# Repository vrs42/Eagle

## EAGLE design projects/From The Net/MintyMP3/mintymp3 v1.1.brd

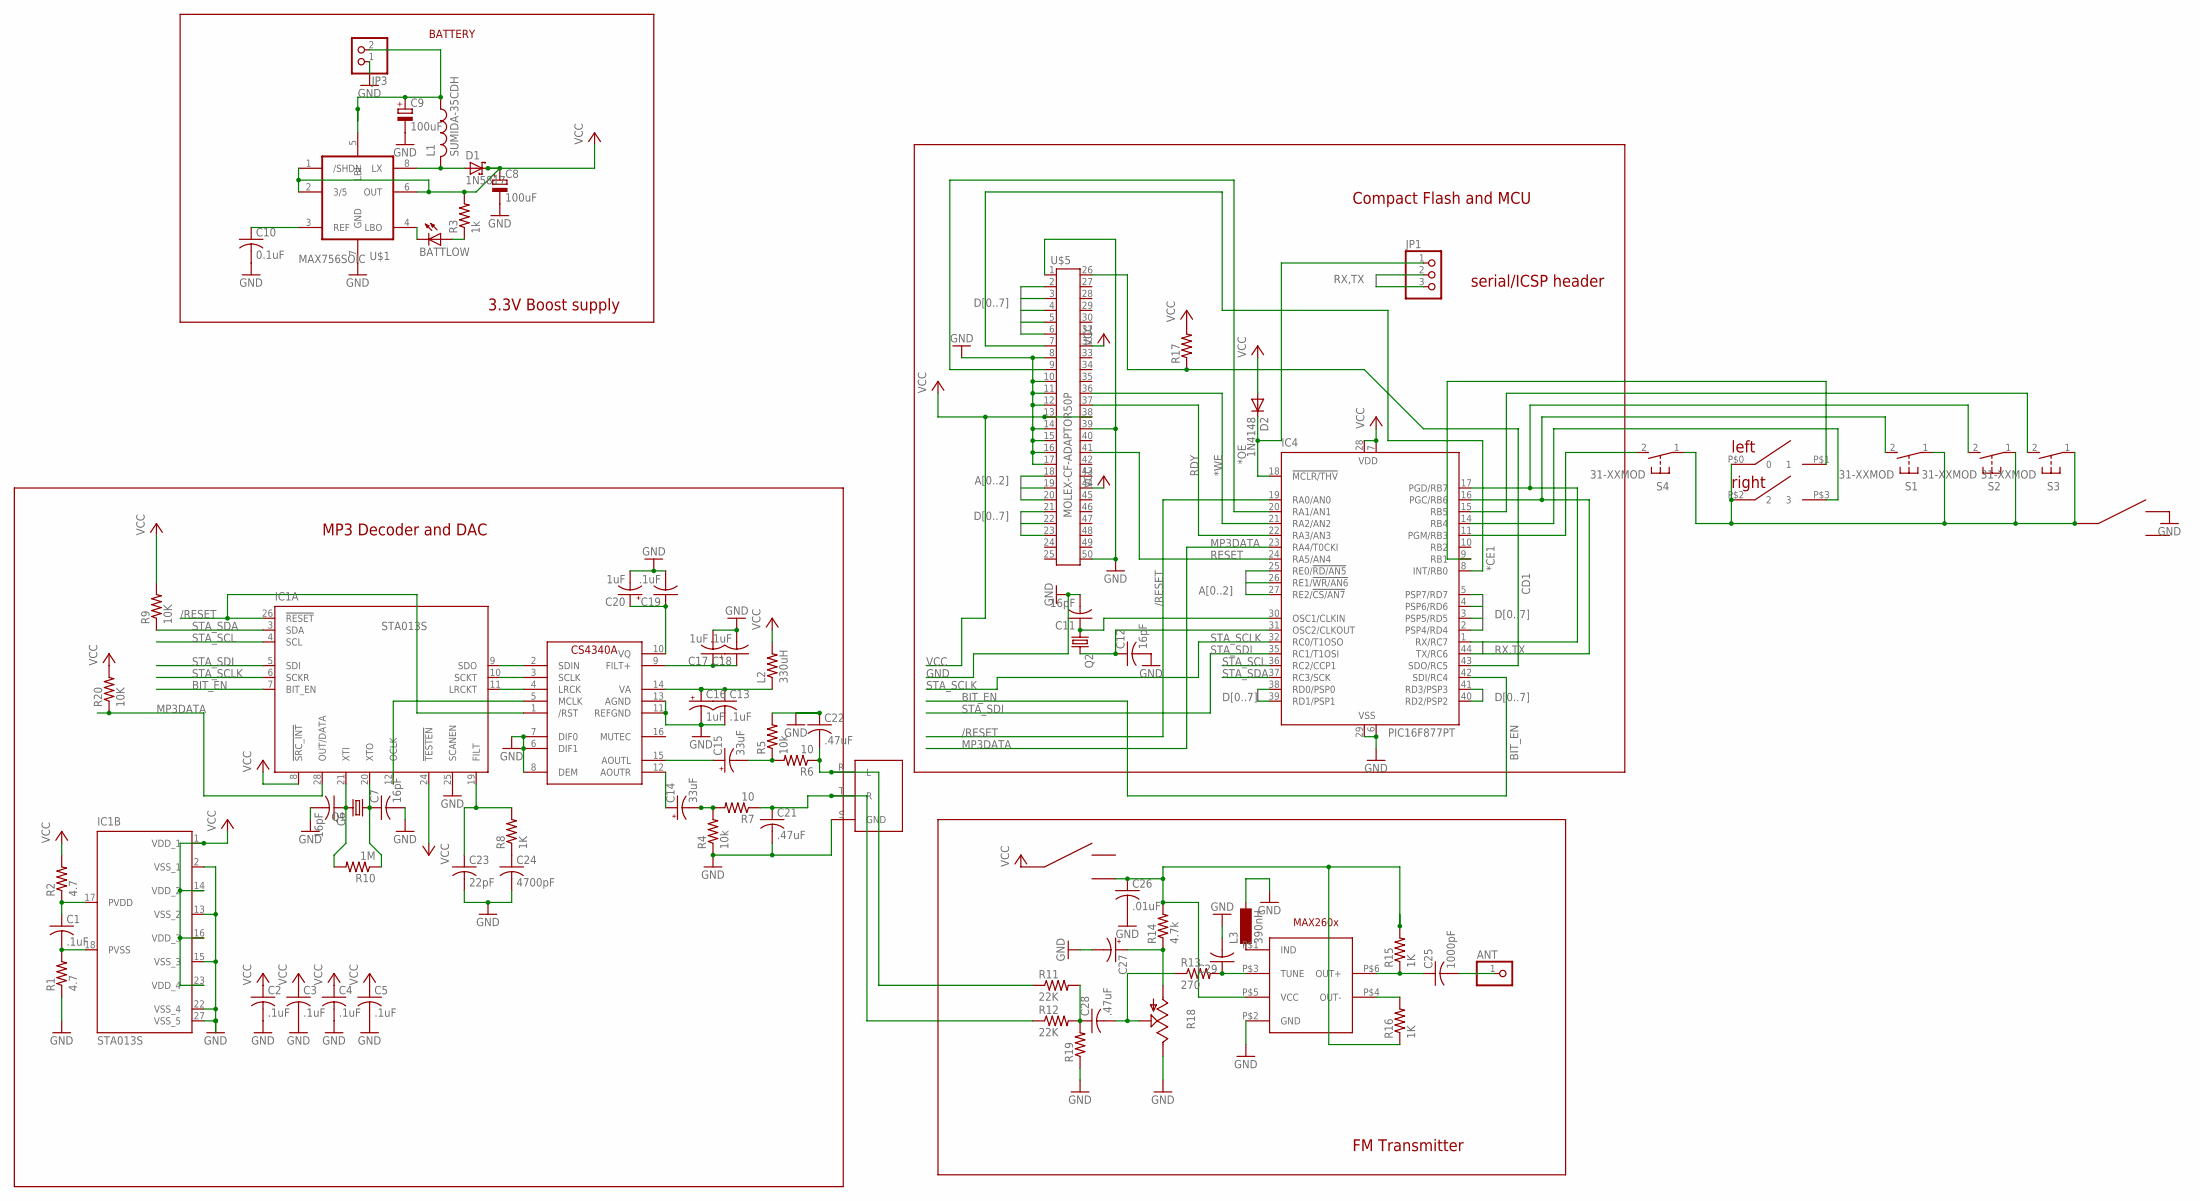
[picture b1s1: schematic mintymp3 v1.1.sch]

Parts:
ANT: PINHD-1X1; 1X01
BATTLOW: LED3MM
C1, C2, C3, C4, C5, C13, C18, C19: .1uF; C1206
C6, C7, C11, C12: 16pF; C1206
C8, C9: 100uF; PANASONIC_D
C10: 0.1uF; C1206
C14, C15: 33uF; PANASONIC_B
C16, C17, C20: 1uF; PANASONIC_A
C21, C22, C28: .47uF; C1206
C23: 22pF; C1206
C24: 4700pF; C1206
C25: 1000pF; C1206
C26: .01uF; C1206
C27: CPOL-USB; PANASONIC_B
C29: C-USC1206; C1206
D1: 1N5817; DO35-7
D2: 1N4148; DO35-10
FM_SWITCH: SLIDE_SW; SLIDESWITCH
HEADPHONE: STEREOJACKSMDMOD; SJ-3523-MODIFIED
IC1: STA013S; SO28W
IC4: PIC16F877PT; TQFP44
JP1: PINHD-1X3; 1X03
JP3: PINHD-1X2; 1X02
L1: SUMIDA-35CDH; CDH53
L2: 330uH; R1210
L3: 390nH; SM-1206
Q1, Q2: CRYSTALHC49UP; HC49UP
R1, R2: 4.7; R1206
R3: 1k; R1206
R4, R5: 10k; R1206
R6, R7: 10; R1206
R8, R15, R16: 1K; R1206
R9, R20: 10K; R1206
R10: 1M; R1206
R11, R12: 22K; R1206
R13: 270; R1206
R14: 4.7k; R1206
R17, R19: R-US_R1206; R1206
R18: TRIM_US-ECP10P; ECP10P
S1, S2, S3, S4: 31-XXMOD; B3F-31XX-MODIFIED
U$1: MAX756SOIC; SO08
U$2: SLIDE_SW; SLIDESWITCH
U$3: TPC_SWITCH; TPC_SCAN
U$4: CS4340A; SO16
U$5: MOLEX-CF-ADAPTOR50P; COMPACTFLASH
U$9: MAX260X; SOT23-6

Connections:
*CE1: IC4.8 (INT/RB0), U$5.7
*OE: IC4.20 (RA1/AN1), U$5.9
*WE: IC4.21 (RA2/AN2), U$5.36
/RESET: IC1.26 (!RESET), IC4.19 (RA0/AN0), U$4.1 (/RST)
A0: IC4.25 (RE0/!RD/AN5), U$5.20
A1: IC4.26 (RE1/!WR/AN6), U$5.19
A2: IC4.27 (RE2/!CS/AN7), U$5.18
ANTENNA: ANT.1, C25.2
BIT_EN: IC1.7 (BIT_EN), IC4.42 (SDI/RC4)
BUTTON1: IC4.11 (PGM/RB3), S4.2 (S)
CD1: IC4.43 (SDO/RC5), R17.1, U$5.26
D0: IC4.38 (RD0/PSP0), U$5.21
D1: IC4.39 (RD1/PSP1), U$5.22
D2: IC4.40 (RD2/PSP2), U$5.23
D3: IC4.41 (RD3/PSP3), U$5.2
D4: IC4.2 (PSP4/RD4), U$5.3
D5: IC4.3 (PSP5/RD5), U$5.4
D6: IC4.4 (PSP6/RD6), U$5.5
D7: IC4.5 (PSP7/RD7), U$5.6
GND: C2.2, C3.2, C4.2, C5.2, C6.2, C7.2, C8.-, C9.-, C10.2, C11.2, C12.2, C13.2, C16.-, C17.-, C18.2, C19.2, C20.-, C21.2, C22.1, C23.2, C24.2, C26.2, C27.-, C29.2, HEADPHONE.S (GND), IC1.2 (VSS_1), IC1.13 (VSS_2), IC1.15 (VSS_3), IC1.22 (VSS_4), IC1.25 (SCANEN), IC1.27 (VSS_5), IC4.6 (VSS), IC4.29 (VSS), JP3.1, L3.2, R1.1, R4.1, R5.2, R18.E, R19.1, U$1.7 (GND), U$2.P$1, U$4.6 (DIF1), U$4.7 (DIF0), U$4.8 (DEM), U$4.11 (REFGND), U$4.13 (AGND), U$5.1, U$5.8, U$5.10, U$5.11, U$5.12, U$5.14, U$5.15, U$5.16, U$5.17, U$5.39, U$5.50, U$9.P$2 (GND)
MCLR: D2.C, IC4.18 (!MCLR/THV), JP1.1
MP3DATA: IC1.28 (OUT/DATA), IC4.23 (RA4/T0CKI), R20.1
unnamed: C26.1, FM_SWITCH.P$3, R14.2, R15.2, R16.1, U$9.P$5 (VCC)
unnamed: C6.1, IC1.21 (XTI), Q1.2, R10.2
unnamed: C7.1, IC1.20 (XTO), Q1.1, R10.1
unnamed: IC4.14 (RB4), U$3.P$3 (3)
unnamed: C1.1, IC1.17 (PVDD), R2.1
unnamed: C1.2, IC1.18 (PVSS), R1.2
unnamed: C9.+, JP3.2, L1.P$1 (1), U$1.5 (LBI)
unnamed: D1.A, L1.P$2 (2), U$1.8 (LX)
unnamed: IC1.9 (SDO), U$4.2 (SDIN)
unnamed: IC1.10 (SCKT), U$4.3 (SCLK)
unnamed: IC1.11 (LRCKT), U$4.4 (LRCK)
unnamed: IC1.12 (OCLK), U$4.5 (MCLK)
unnamed: IC4.9 (RB1), U$3.P$1 (1)
unnamed: IC4.15 (RB5), S3.2 (S)
unnamed: C15.+, U$4.15 (AOUTL)
unnamed: C10.1, U$1.3 (REF)
unnamed: BATTLOW.A, R3.1
unnamed: BATTLOW.K (C), U$1.4 (LBO)
unnamed: C13.1, C16.+, L2.1, U$4.14 (VA)
unnamed: C11.1, IC4.30 (OSC1/CLKIN), Q2.1
unnamed: C12.1, IC4.31 (OSC2/CLKOUT), Q2.2
unnamed: C14.+, U$4.12 (AOUTR)
unnamed: C14.-, R4.2, R7.2
unnamed: C15.-, R5.1, R6.2
unnamed: C22.2, HEADPHONE.R (L), R6.1, R11.1
unnamed: C17.+, C18.1, U$4.9 (FILT+)
unnamed: C19.1, C20.+, U$4.10 (VQ)
unnamed: C29.1, R13.2, U$9.P$3 (TUNE)
unnamed: C24.1, R8.1
unnamed: C23.1, IC1.19 (FILT), R8.2
unnamed: C25.1, R15.1, U$9.P$6 (OUT+)
unnamed: R16.2, U$9.P$4 (OUT-)
unnamed: C21.1, HEADPHONE.T (R), R7.1, R12.1
unnamed: C28.1, R11.2, R12.2, R19.2
unnamed: C27.+, R14.1, R18.A
unnamed: C28.2, R13.1, R18.S
unnamed: L3.1, U$9.P$1 (IND)
unnamed: S1.1, S2.1, S3.1, S4.1, U$2.P$2, U$3.P$0 (0), U$3.P$2 (2)
RDY: IC4.22 (RA3/AN3), U$5.37
RESET: IC4.24 (RA5/AN4), U$5.41
RX: IC4.1 (RX/RC7), IC4.17 (PGD/RB7), JP1.2, S2.2 (S)
STA_SCL: IC1.4 (SCL), IC4.36 (RC2/CCP1)
STA_SCLK: IC1.6 (SCKR), IC4.32 (RC0/T1OSO)
STA_SDA: IC1.3 (SDA), IC4.37 (RC3/SCK), R9.1
STA_SDI: IC1.5 (SDI), IC4.35 (RC1/T1OSI)
TX: IC4.16 (PGC/RB6), IC4.44 (TX/RC6), JP1.3, S1.2 (S)
VCC: C2.1, C3.1, C4.1, C5.1, C8.+, D1.C, D2.A, FM_SWITCH.P$2, IC1.1 (VDD_1), IC1.8 (!SRC_INT), IC1.14 (VDD_2), IC1.16 (VDD_3), IC1.23 (VDD_4), IC1.24 (!TESTEN), IC4.7 (VDD), IC4.28 (VDD), L2.2, R2.2, R3.2, R9.2, R17.2, R20.2, U$1.1 (/SHDN), U$1.2 (3/5), U$1.6 (OUT), U$5.13, U$5.32, U$5.38, U$5.44

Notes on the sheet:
3.3V Boost supply
BATTERY
Compact Flash and MCU
MP3 Decoder and DAC
FM Transmitter
serial/ICSP header

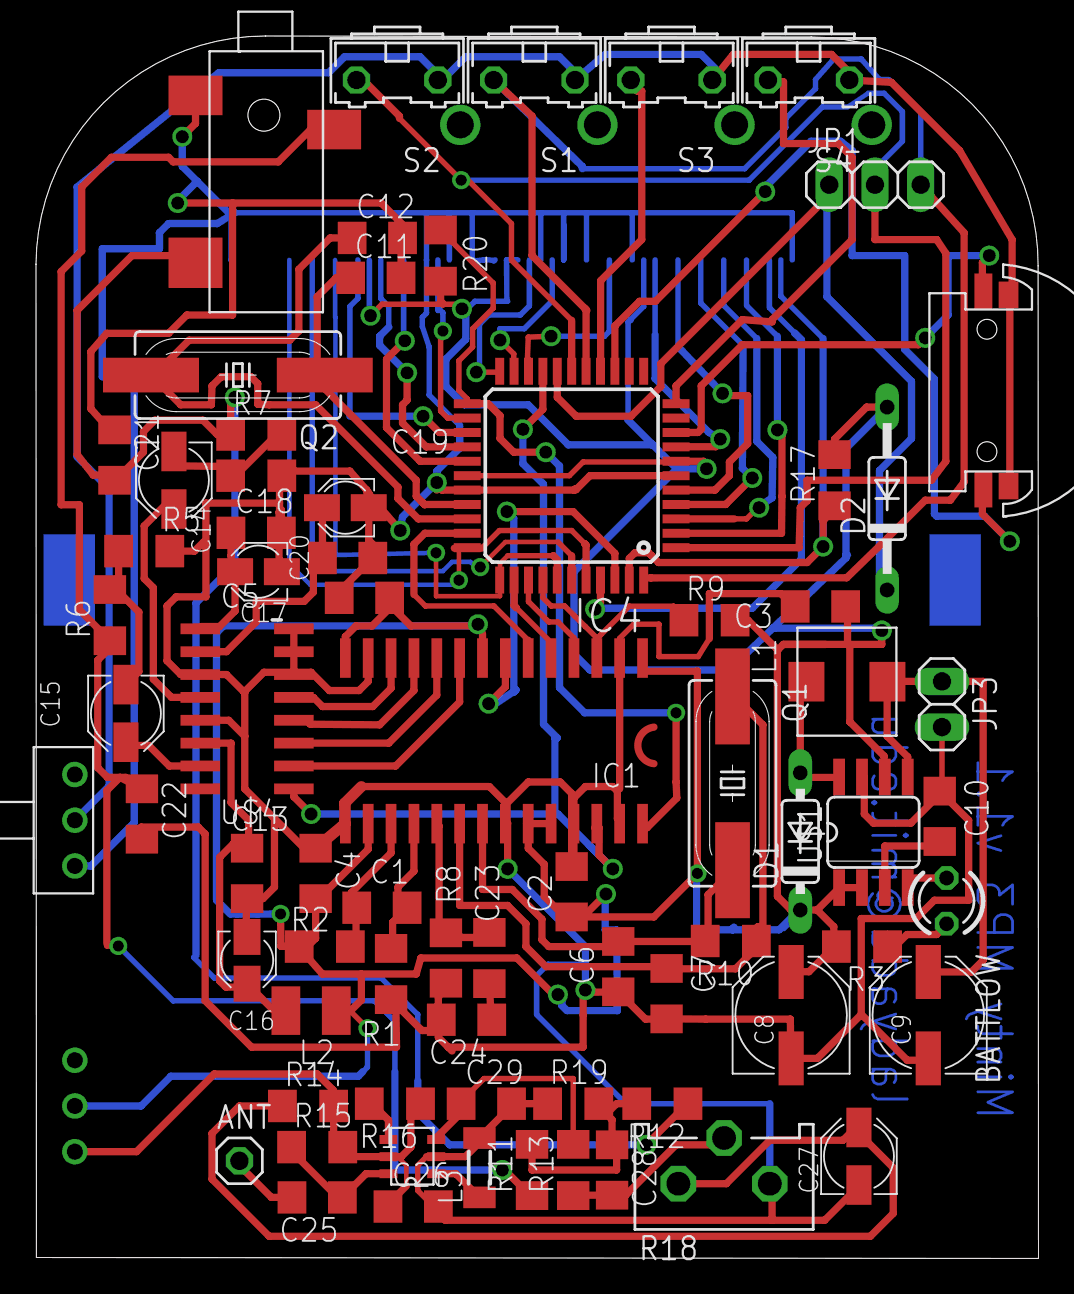
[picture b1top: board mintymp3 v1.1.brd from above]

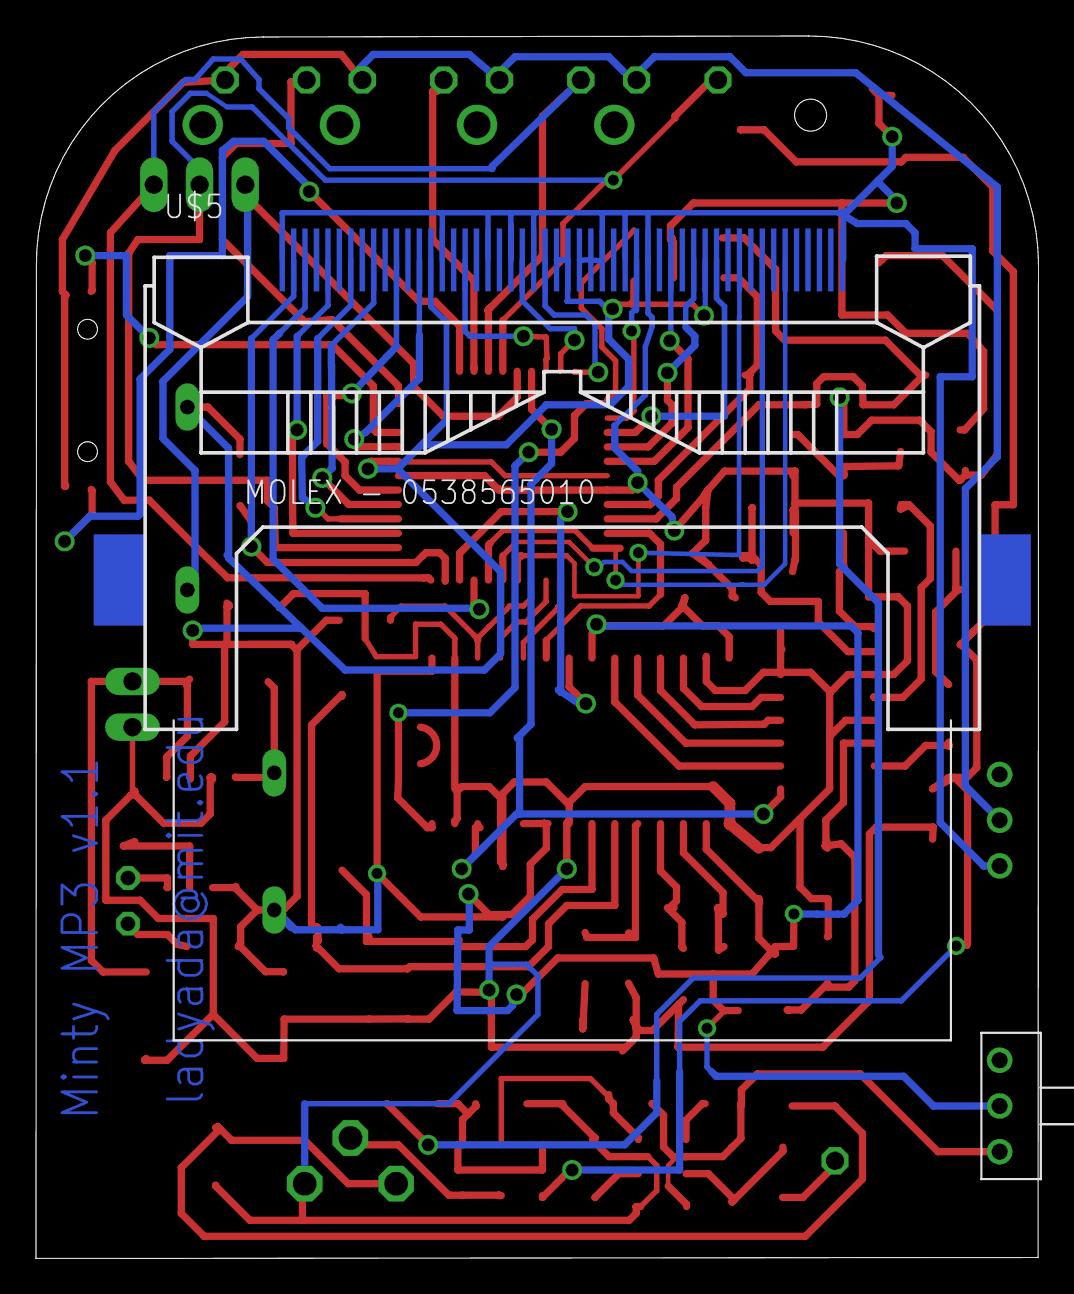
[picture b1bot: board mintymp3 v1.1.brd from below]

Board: 2 copper layers, 55.7 x 67.9 mm, 74 parts (2 on the bottom side), 69 nets.

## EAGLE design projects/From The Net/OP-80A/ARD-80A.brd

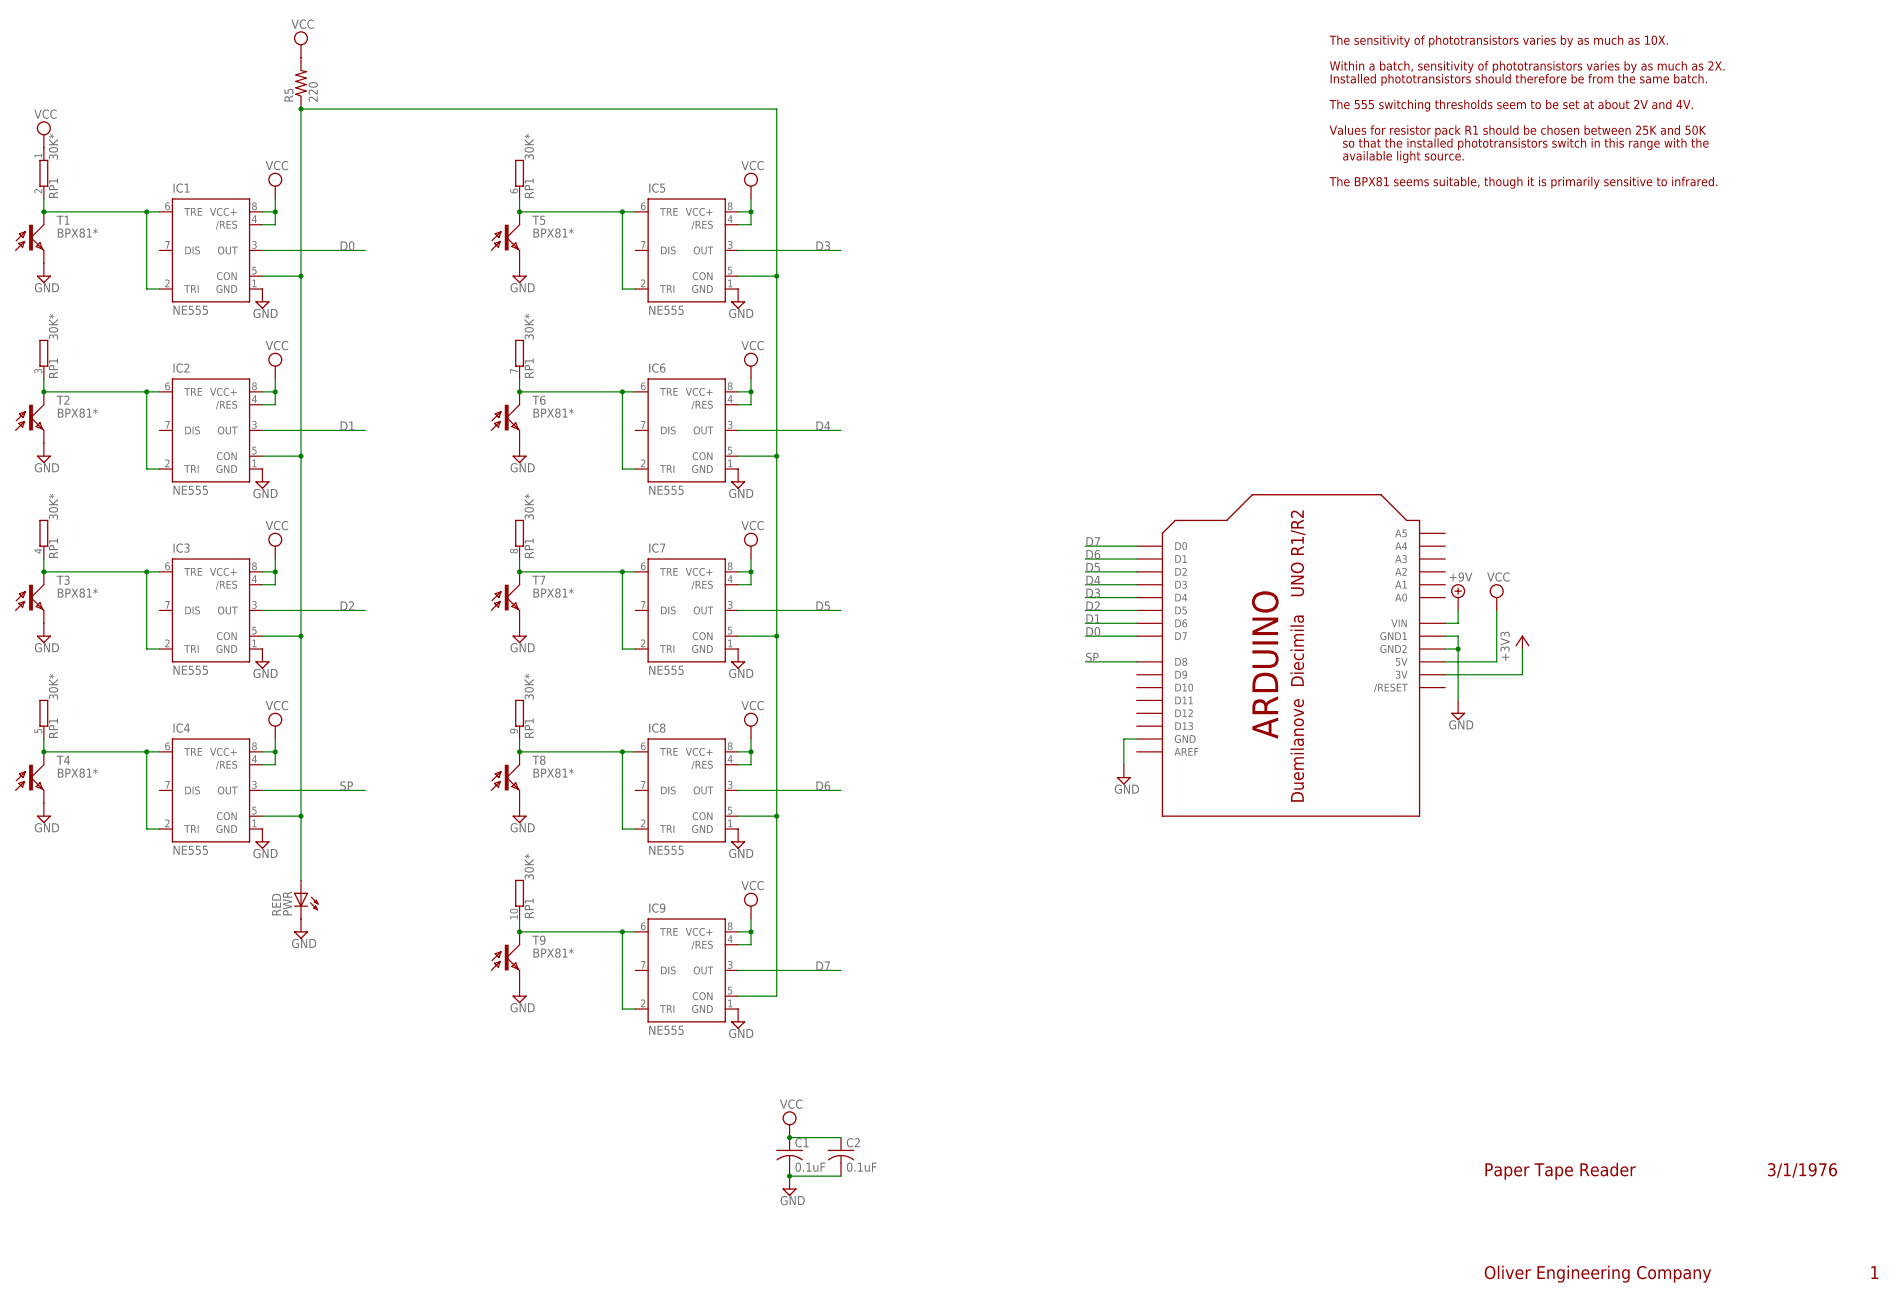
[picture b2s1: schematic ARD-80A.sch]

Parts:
C1, C2: 0.1uF; C050-030X075
IC1, IC2, IC3, IC4, IC5, IC6, IC7, IC8, IC9: NE555; DIL-08
PWR: RED; LED5MM
R5: 220; 0207/10
RP1: 30K*; SIL10
T1, T2, T3, T4, T5, T6, T7, T8, T9: BPX81*; BPX81
U$2: ARDUINODUE; ARDUINO_DUE_SHIELD

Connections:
+3V3: U$2.3V3 (3V)
+9V: U$2.VIN
D0: IC1.3 (OUT), U$2.7 (D7)
D1: IC2.3 (OUT), U$2.6 (D6)
D2: IC3.3 (OUT), U$2.5 (D5)
D3: IC5.3 (OUT), U$2.4 (D4)
D4: IC6.3 (OUT), U$2.3 (D3)
D5: IC7.3 (OUT), U$2.2 (D2)
D6: IC8.3 (OUT), U$2.1 (D1)
D7: IC9.3 (OUT), U$2.0 (D0)
GND: C1.2, C2.2, IC1.1 (GND), IC2.1 (GND), IC3.1 (GND), IC4.1 (GND), IC5.1 (GND), IC6.1 (GND), IC7.1 (GND), IC8.1 (GND), IC9.1 (GND), PWR.K (C), T1.E, T2.E, T3.E, T4.E, T5.E, T6.E, T7.E, T8.E, T9.E, U$2.GND, U$2.GND_1 (GND1), U$2.GND_2 (GND2)
unnamed: IC1.2 (TRI), IC1.6 (TRE), RP1.2, T1.C
unnamed: IC1.5 (CON), IC2.5 (CON), IC3.5 (CON), IC4.5 (CON), IC5.5 (CON), IC6.5 (CON), IC7.5 (CON), IC8.5 (CON), IC9.5 (CON), PWR.A, R5.1
unnamed: IC2.2 (TRI), IC2.6 (TRE), RP1.3 (2), T2.C
unnamed: IC3.2 (TRI), IC3.6 (TRE), RP1.4 (2), T3.C
unnamed: IC9.2 (TRI), IC9.6 (TRE), RP1.10 (2), T9.C
unnamed: IC4.2 (TRI), IC4.6 (TRE), RP1.5 (2), T4.C
unnamed: IC5.2 (TRI), IC5.6 (TRE), RP1.6 (2), T5.C
unnamed: IC6.2 (TRI), IC6.6 (TRE), RP1.7 (2), T6.C
unnamed: IC7.2 (TRI), IC7.6 (TRE), RP1.8 (2), T7.C
unnamed: IC8.2 (TRI), IC8.6 (TRE), RP1.9 (2), T8.C
SP: IC4.3 (OUT), U$2.8 (D8)
VCC: C1.1, C2.1, IC1.4 (/RES), IC1.8 (VCC+), IC2.4 (/RES), IC2.8 (VCC+), IC3.4 (/RES), IC3.8 (VCC+), IC4.4 (/RES), IC4.8 (VCC+), IC5.4 (/RES), IC5.8 (VCC+), IC6.4 (/RES), IC6.8 (VCC+), IC7.4 (/RES), IC7.8 (VCC+), IC8.4 (/RES), IC8.8 (VCC+), IC9.4 (/RES), IC9.8 (VCC+), R5.2, RP1.1, U$2.5V0 (5V)

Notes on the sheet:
Oliver Engineering Company
Paper Tape Reader
3/1/1976
The sensitivity of phototransistors varies by as much as 10X.
Within a batch, sensitivity of phototransistors varies by as much as 2X.
The 555 switching thresholds seem to be set at about 2V and 4V.
Values for resistor pack R1 should be chosen between 25K and 50K
Installed phototransistors should therefore be from the same batch.
so that the installed phototransistors switch in this range with the
available light source.
The BPX81 seems suitable, though it is primarily sensitive to infrared.

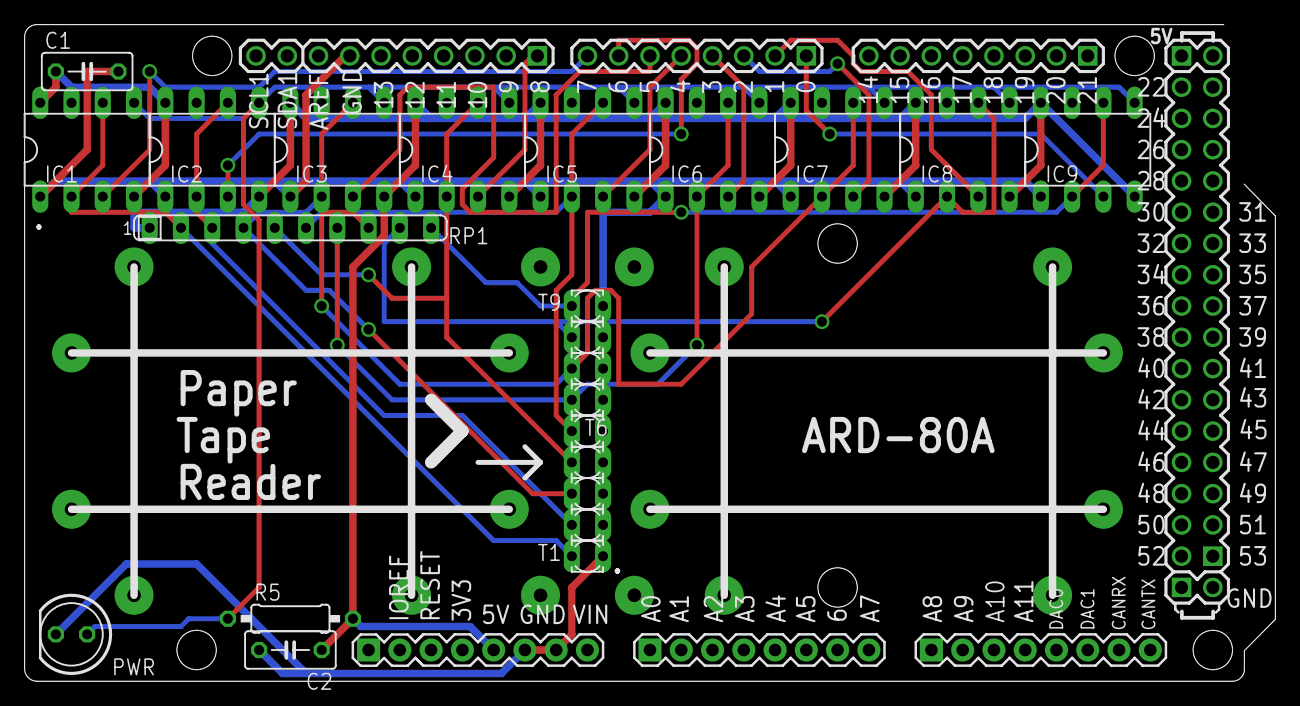
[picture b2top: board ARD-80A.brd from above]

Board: 2 copper layers, 101.6 x 53.3 mm, 24 parts (0 on the bottom side), 21 nets.

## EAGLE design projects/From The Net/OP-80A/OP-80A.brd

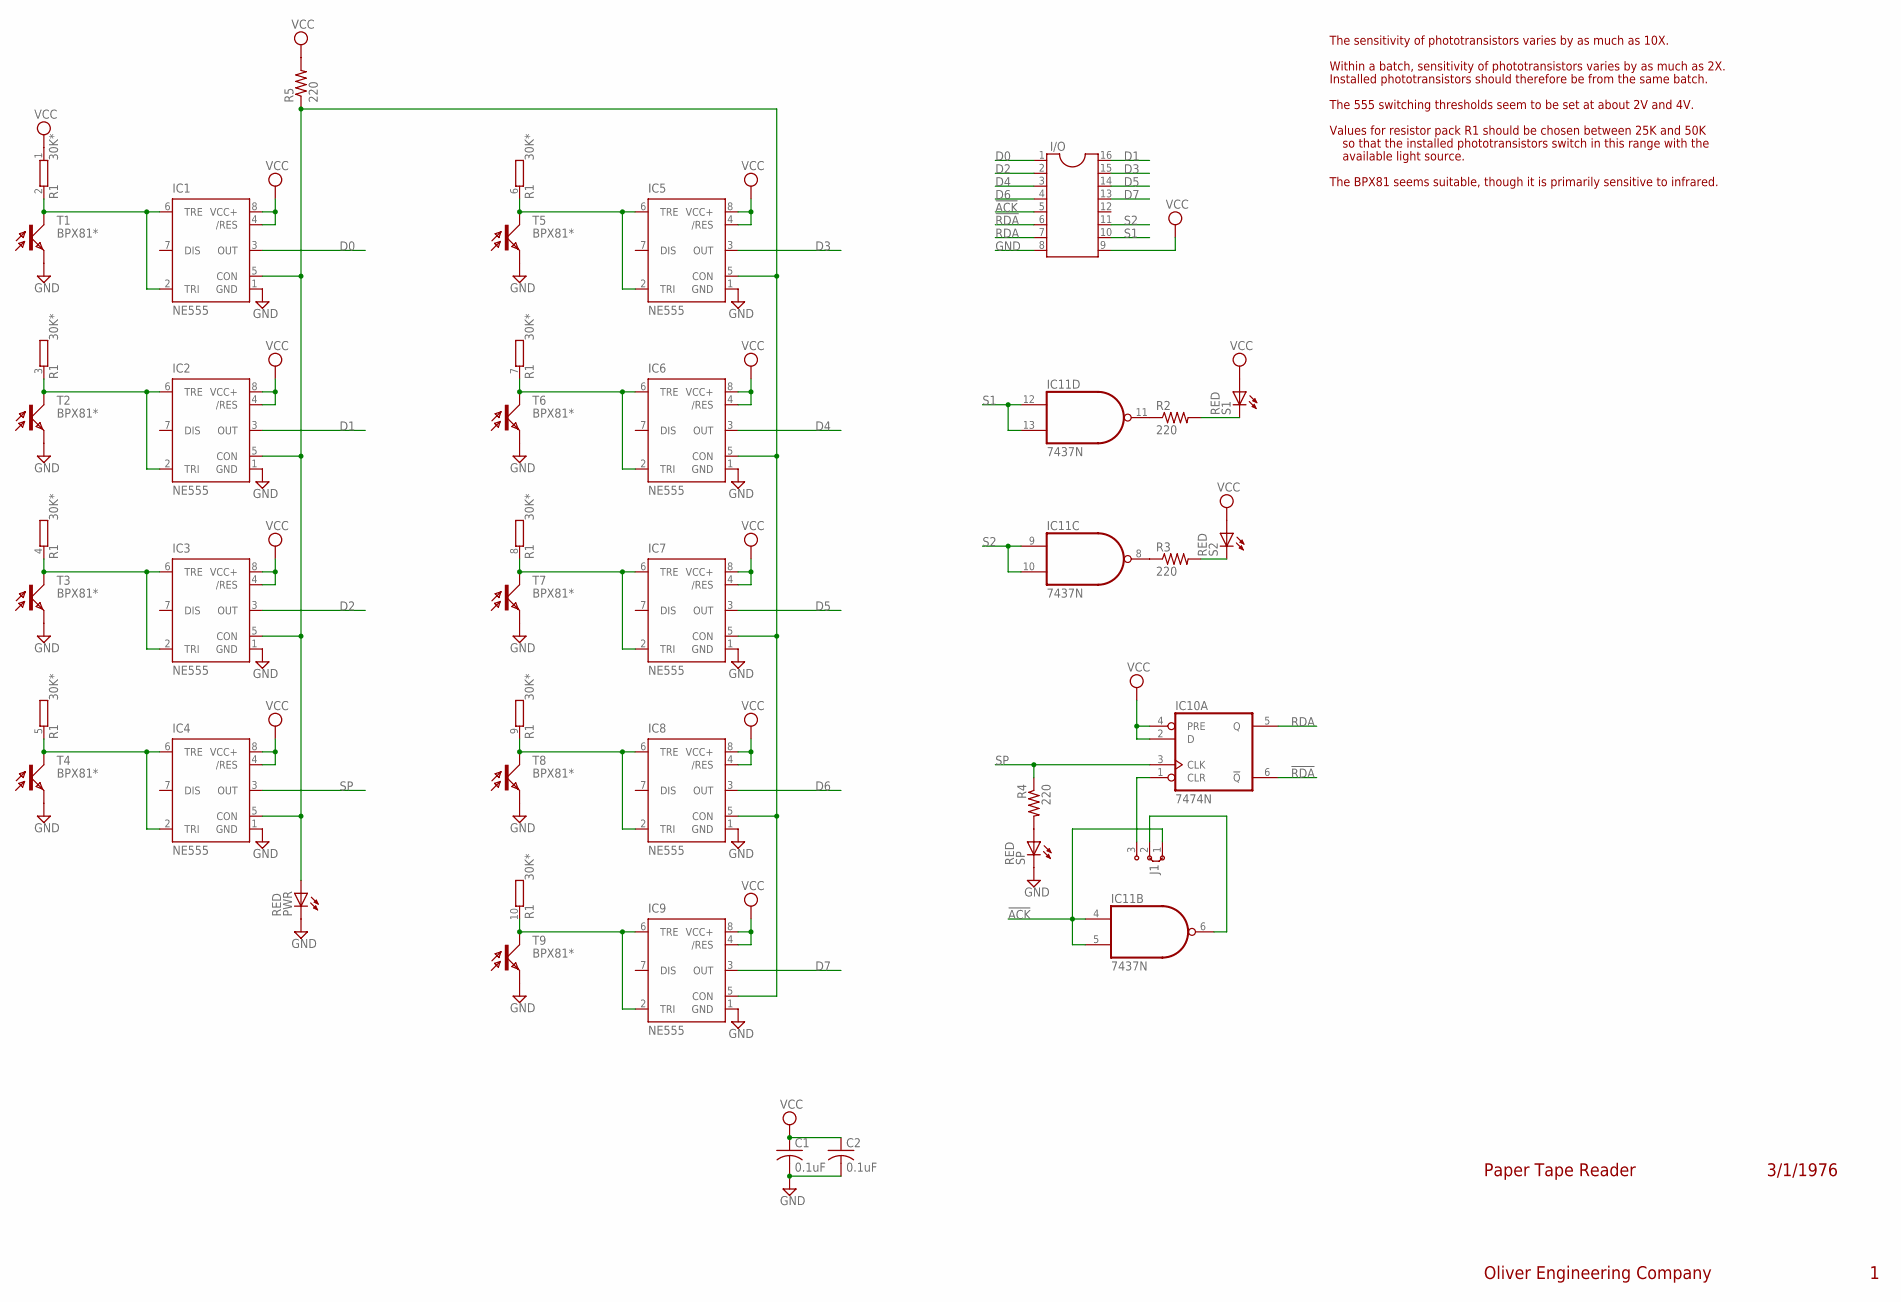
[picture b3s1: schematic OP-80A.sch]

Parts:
C1, C2: 0.1uF; C050-030X075
I/O: DIL16S; SOCKET-16
IC1, IC2, IC3, IC4, IC5, IC6, IC7, IC8, IC9: NE555; DIL-08
IC10: 7474N; DIL14
IC11: 7437N; DIL14
J1: J2X5MM; 05C
PWR: RED; LED5MM
R1: 30K*; SIL10
R2, R3, R4, R5: 220; 0207/10
S1, S2: RED; LED5MM
SP: RED; LED5MM
T1, T2, T3, T4, T5, T6, T7, T8, T9: BPX81*; BPX81

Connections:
!ACK: I/O.5, IC11.4 (I0), IC11.5 (I1), J1.1
!RDA: I/O.6, IC10.6 (!Q)
ACK: IC11.6 (O), J1.2
D0: I/O.1, IC1.3 (OUT)
D1: I/O.16, IC2.3 (OUT)
D2: I/O.2, IC3.3 (OUT)
D3: I/O.15, IC5.3 (OUT)
D4: I/O.3, IC6.3 (OUT)
D5: I/O.14, IC7.3 (OUT)
D6: I/O.4, IC8.3 (OUT)
D7: I/O.13, IC9.3 (OUT)
GND: C1.2, C2.2, I/O.8, IC1.1 (GND), IC2.1 (GND), IC3.1 (GND), IC4.1 (GND), IC5.1 (GND), IC6.1 (GND), IC7.1 (GND), IC8.1 (GND), IC9.1 (GND), IC10.7 (GND), IC11.7 (GND), PWR.K (C), SP.K (C), T1.E, T2.E, T3.E, T4.E, T5.E, T6.E, T7.E, T8.E, T9.E
unnamed: IC1.2 (TRI), IC1.6 (TRE), R1.2, T1.C
unnamed: R4.2, SP.A
unnamed: IC1.5 (CON), IC2.5 (CON), IC3.5 (CON), IC4.5 (CON), IC5.5 (CON), IC6.5 (CON), IC7.5 (CON), IC8.5 (CON), IC9.5 (CON), PWR.A, R5.1
unnamed: IC2.2 (TRI), IC2.6 (TRE), R1.3 (2), T2.C
unnamed: IC3.2 (TRI), IC3.6 (TRE), R1.4 (2), T3.C
unnamed: IC11.11 (O), R2.1
unnamed: IC9.2 (TRI), IC9.6 (TRE), R1.10 (2), T9.C
unnamed: IC4.2 (TRI), IC4.6 (TRE), R1.5 (2), T4.C
unnamed: IC11.8 (O), R3.1
unnamed: R2.2, S1.K (C)
unnamed: IC5.2 (TRI), IC5.6 (TRE), R1.6 (2), T5.C
unnamed: R3.2, S2.K (C)
unnamed: IC6.2 (TRI), IC6.6 (TRE), R1.7 (2), T6.C
unnamed: IC7.2 (TRI), IC7.6 (TRE), R1.8 (2), T7.C
unnamed: IC8.2 (TRI), IC8.6 (TRE), R1.9 (2), T8.C
RDA: I/O.7, IC10.5 (Q)
S1: I/O.10, IC11.12 (I0), IC11.13 (I1)
S2: I/O.11, IC11.9 (I0), IC11.10 (I1)
SACK: IC10.1 (CLR), J1.3
SP: IC4.3 (OUT), IC10.3 (CLK), R4.1
VCC: C1.1, C2.1, I/O.9, IC1.4 (/RES), IC1.8 (VCC+), IC2.4 (/RES), IC2.8 (VCC+), IC3.4 (/RES), IC3.8 (VCC+), IC4.4 (/RES), IC4.8 (VCC+), IC5.4 (/RES), IC5.8 (VCC+), IC6.4 (/RES), IC6.8 (VCC+), IC7.4 (/RES), IC7.8 (VCC+), IC8.4 (/RES), IC8.8 (VCC+), IC9.4 (/RES), IC9.8 (VCC+), IC10.2 (D), IC10.4 (PRE), IC10.14 (VCC), IC11.14 (VCC), R1.1, R5.2, S1.A, S2.A

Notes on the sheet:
Oliver Engineering Company
Paper Tape Reader
3/1/1976
The sensitivity of phototransistors varies by as much as 10X.
Within a batch, sensitivity of phototransistors varies by as much as 2X.
The 555 switching thresholds seem to be set at about 2V and 4V.
Values for resistor pack R1 should be chosen between 25K and 50K
Installed phototransistors should therefore be from the same batch.
so that the installed phototransistors switch in this range with the
available light source.
The BPX81 seems suitable, though it is primarily sensitive to infrared.

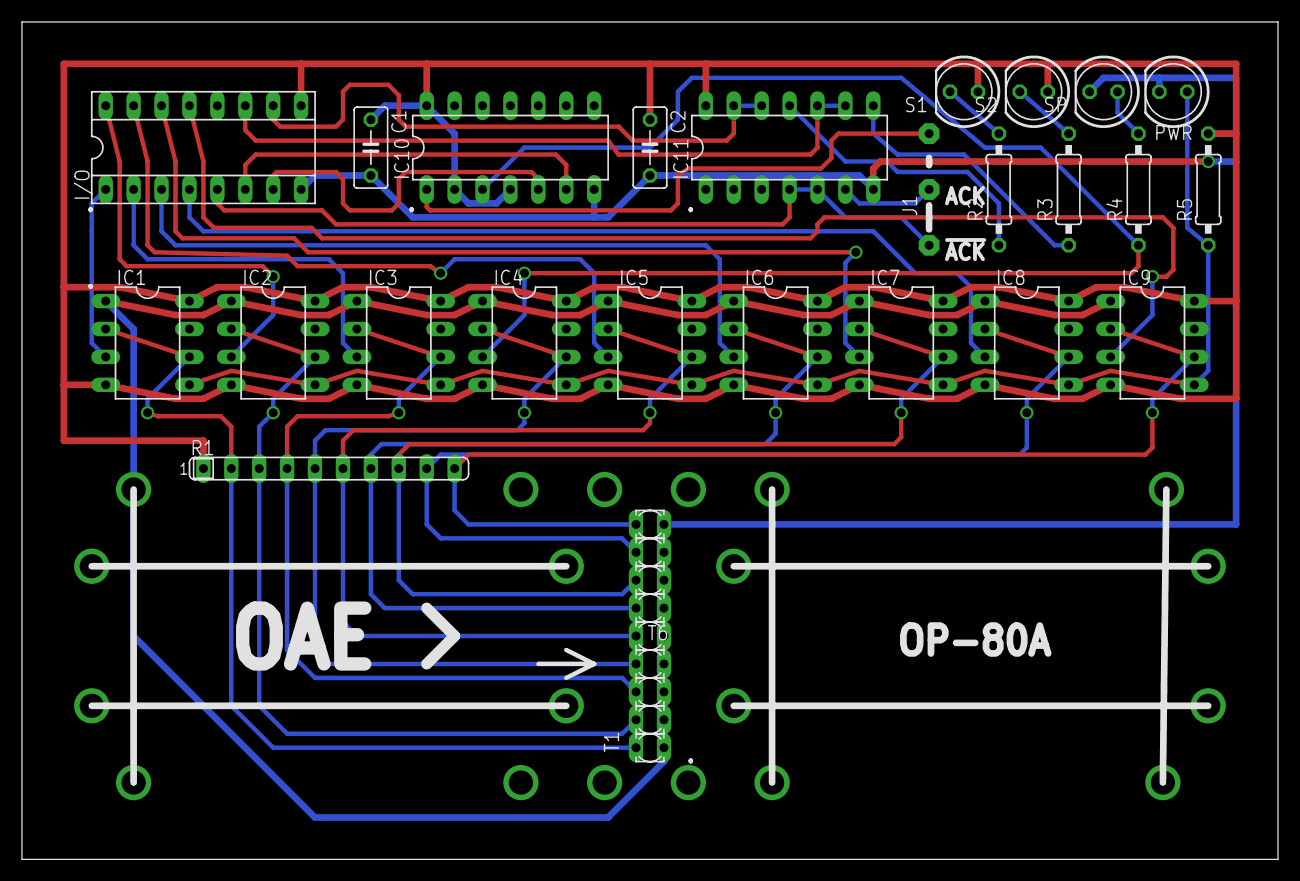
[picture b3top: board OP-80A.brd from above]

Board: 2 copper layers, 114.3 x 76.2 mm, 33 parts (0 on the bottom side), 33 nets.
